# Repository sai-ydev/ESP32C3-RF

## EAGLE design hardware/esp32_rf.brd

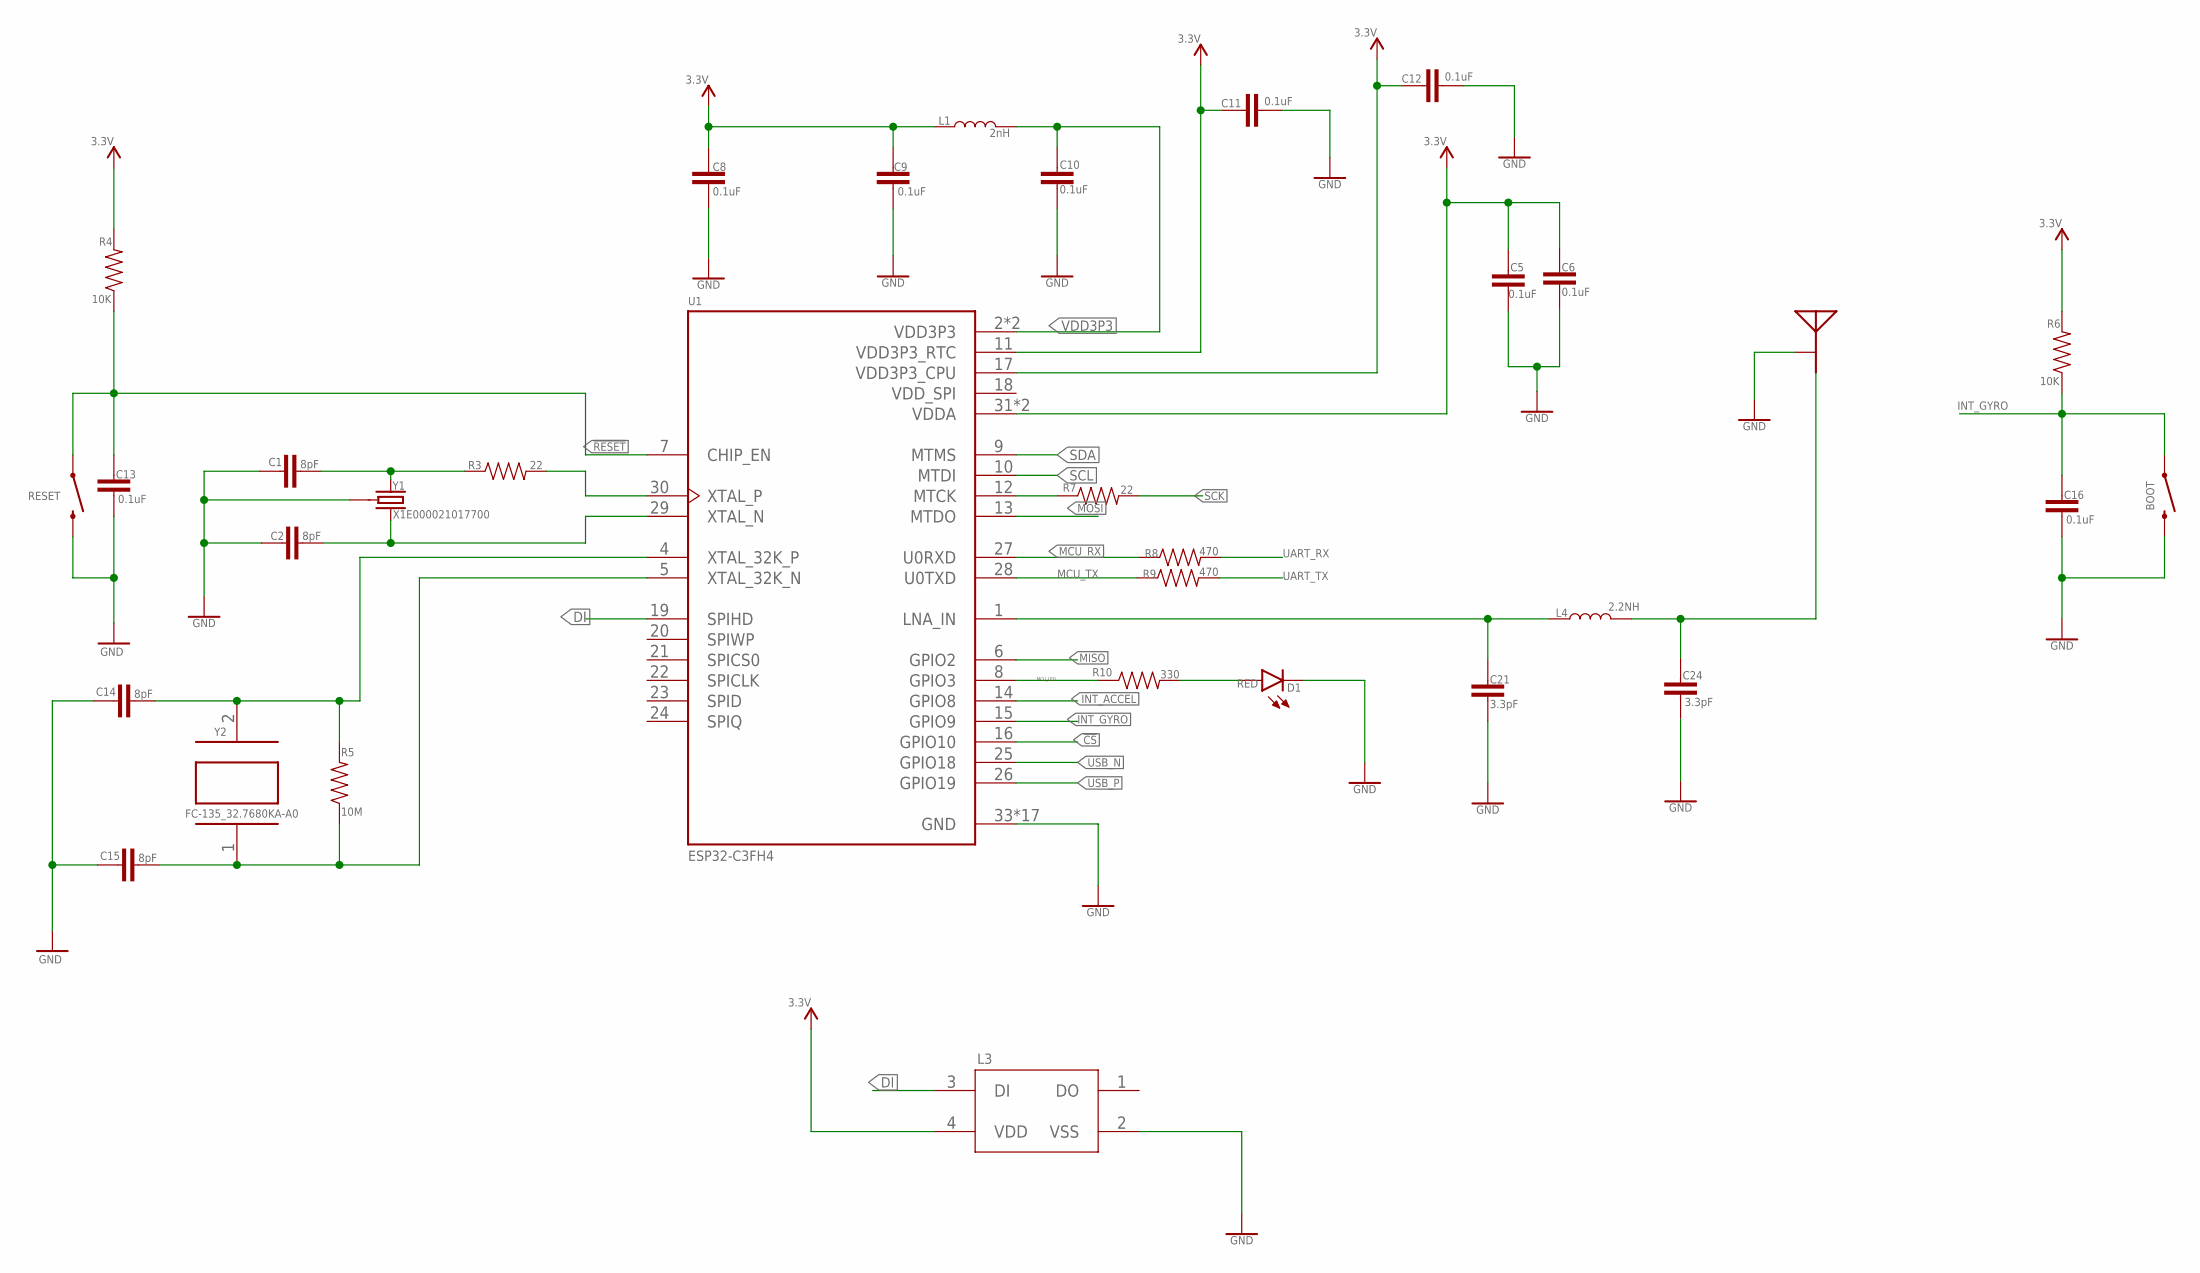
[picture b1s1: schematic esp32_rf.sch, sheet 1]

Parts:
BOOT: MOMENTARY-SWITCH-SPST-SMD-4.6X2.8MM; TACTILE_SWITCH_SMD_4.6X2.8MM
C1, C2, C14, C15: 8pF; 0402
C5, C6, C8, C9, C10, C11, C12, C13, C16: 0.1uF; 0402
C21, C24: 3.3pF; 0402
D1: RED; LED-0603
L1: 2nH; 0402
L3: WS2812B-2020
L4: 2.2NH; 0402
R3, R7: 22; 0402
R4, R6: 10K; 0402
R5: 10M; 0402
R8, R9: 470; 0402
R10: 330; 0402
RESET: MOMENTARY-SWITCH-SPST-SMD-4.6X2.8MM; TACTILE_SWITCH_SMD_4.6X2.8MM
U1: ESP32-C3FH4; QFN50P500X500X90-33N
U$1: MEANDER-ANT
Y1: X1E000021017700; CRYSTAL-SMD-3.2X2.5MM
Y2: FC-135_32.7680KA-A0; XTAL_FC-135_32.7680KA-A0

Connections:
3.3V: C5.1, C6.1, C8.1, C9.2, C11.2, C12.2, L1.1, L3.4 (VDD), R4.2, R6.2, U1.11 (VDD3P3_RTC), U1.17 (VDD3P3_CPU), U1.31 (VDDA), U1.32 (VDDA); also elsewhere on the board
!CS: U1.16 (GPIO10); also elsewhere on the board
!RESET: C13.1, R4.1, RESET.1, RESET.2 (1), U1.7 (CHIP_EN)
DI: L3.3 (DI), U1.19 (SPIHD)
GND: BOOT.3 (2), BOOT.4 (2), C1.1, C2.1, C5.2, C6.2, C8.2, C9.1, C10.1, C11.1, C12.1, C13.2, C14.1, C15.1, C16.2, C21.2, C24.2, D1.C, L3.2 (VSS), RESET.3 (2), RESET.4 (2), U1.33 (GND), U1.34 (GND), U1.35 (GND), U1.36 (GND), U1.37 (GND), U1.38 (GND), U1.39 (GND), U1.40 (GND), U1.41 (GND), U1.42 (GND), U1.43 (GND), U1.44 (GND), U1.45 (GND), U1.46 (GND), U1.47 (GND), U1.48 (GND), U1.49 (GND), U$1.GND, Y1.2 (3), Y1.4 (3); also elsewhere on the board
INT_ACCEL: U1.14 (GPIO8); also elsewhere on the board
INT_GYRO: BOOT.1, BOOT.2 (1), C16.1, R6.1, U1.15 (GPIO9); also elsewhere on the board
MCU_LED: R10.1, U1.8 (GPIO3)
MCU_RX: R8.1, U1.27 (U0RXD)
MCU_TX: R9.1, U1.28 (U0TXD)
MISO: U1.6 (GPIO2); also elsewhere on the board
MOSI: U1.13 (MTDO); also elsewhere on the board
unnamed: R3.2, U1.30 (XTAL_P)
unnamed: C1.2, R3.1, Y1.1
unnamed: C2.2, U1.29 (XTAL_N), Y1.3 (2)
unnamed: C21.1, L4.1, U1.1 (LNA_IN)
unnamed: C24.1, L4.2, U$1.FEED
unnamed: D1.A, R10.2
unnamed: C14.2, R5.2, U1.4 (XTAL_32K_P), Y2.2
unnamed: C15.2, R5.1, U1.5 (XTAL_32K_N), Y2.1
unnamed: R7.1, U1.12 (MTCK)
SCK: R7.2; also elsewhere on the board
SCL: U1.10 (MTDI); also elsewhere on the board
SDA: U1.9 (MTMS); also elsewhere on the board
UART_RX: R8.2; also elsewhere on the board
UART_TX: R9.2; also elsewhere on the board
USB_N: U1.25 (GPIO18); also elsewhere on the board
USB_P: U1.26 (GPIO19); also elsewhere on the board
VDD3P3: C10.2, L1.2, U1.2 (VDD3P3), U1.3 (VDD3P3)
VDD_SPI: U1.18 (VDD_SPI)

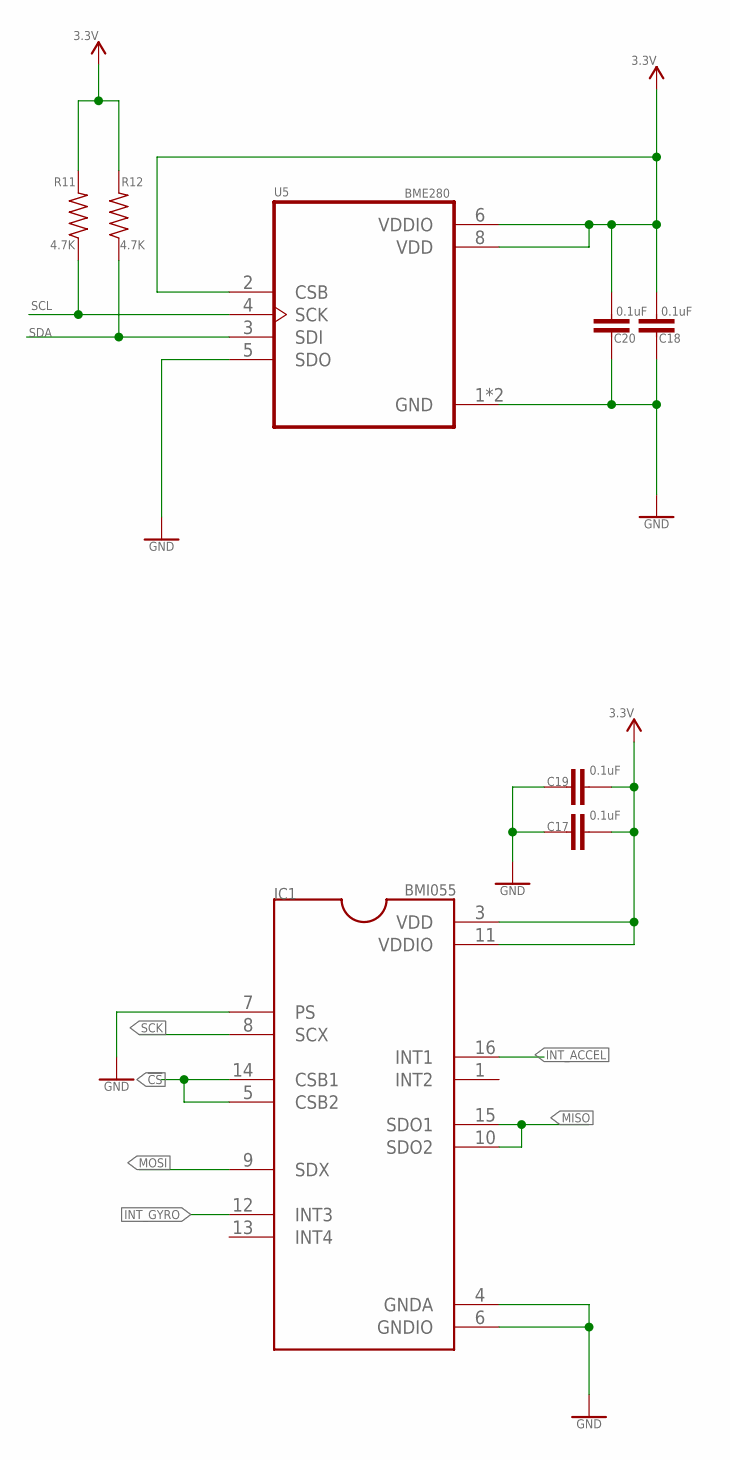
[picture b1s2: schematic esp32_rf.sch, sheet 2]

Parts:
C17, C18, C19, C20: 0.1uF; 0402
IC1: BMI055; QFN50P300X450X100-16N
R11, R12: 4.7K; 0402
U5: BME280; PSON65P250X250X100-8N

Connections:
3.3V: C17.2, C18.2, C19.2, C20.2, IC1.3 (VDD), IC1.11 (VDDIO), R11.2, R12.2, U5.2 (CSB), U5.6 (VDDIO), U5.8 (VDD); also elsewhere on the board
!CS: IC1.5 (CSB2), IC1.14 (CSB1); also elsewhere on the board
GND: C17.1, C18.1, C19.1, C20.1, IC1.4 (GNDA), IC1.6 (GNDIO), IC1.7 (PS), U5.1 (GND), U5.5 (SDO), U5.7 (GND); also elsewhere on the board
INT_ACCEL: IC1.16 (INT1); also elsewhere on the board
INT_GYRO: IC1.12 (INT3); also elsewhere on the board
MISO: IC1.10 (SDO2), IC1.15 (SDO1); also elsewhere on the board
MOSI: IC1.9 (SDX); also elsewhere on the board
SCK: IC1.8 (SCX); also elsewhere on the board
SCL: R11.1, U5.4 (SCK); also elsewhere on the board
SDA: R12.1, U5.3 (SDI); also elsewhere on the board

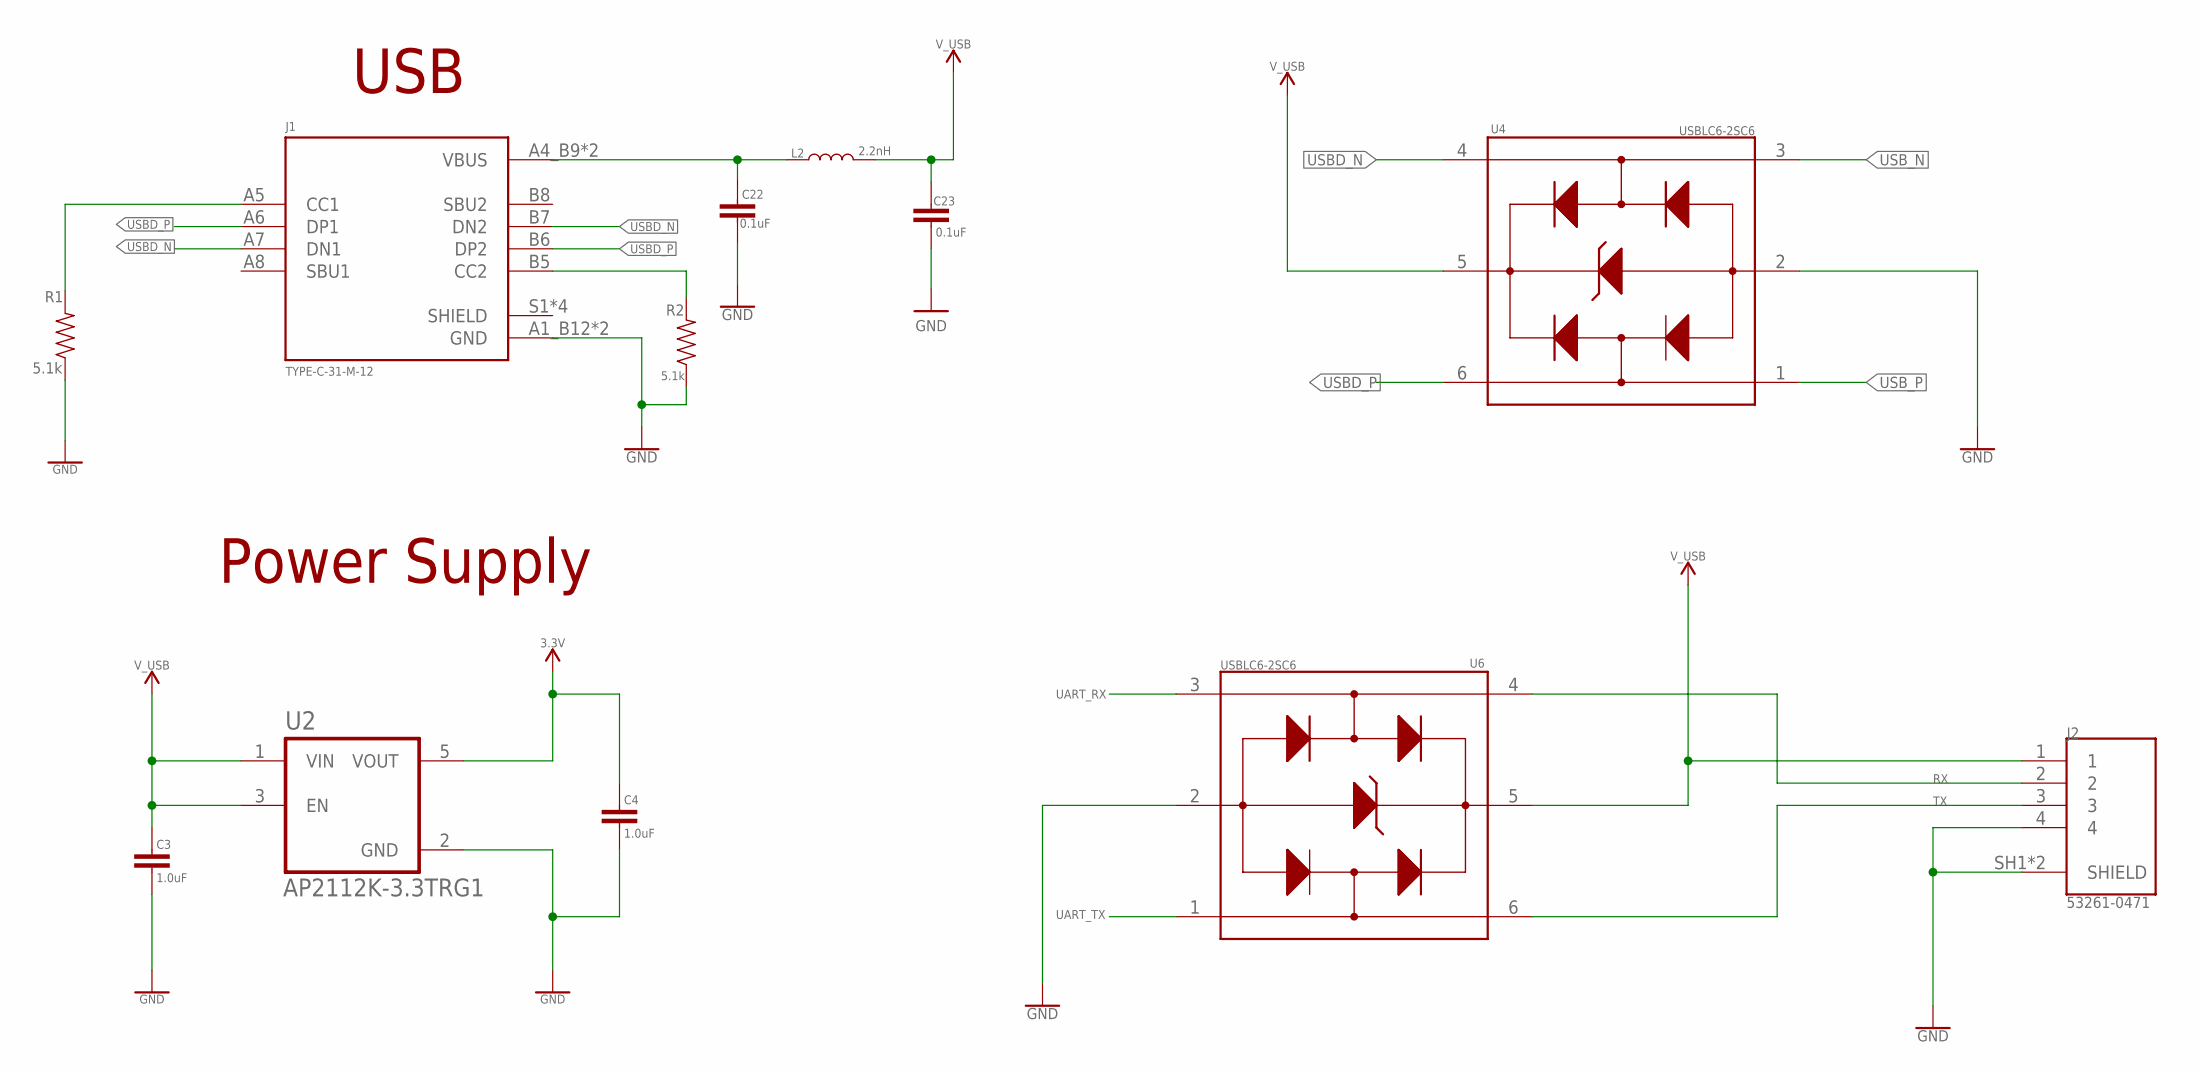
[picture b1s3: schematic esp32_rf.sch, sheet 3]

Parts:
C3, C4: 1.0uF; 0402
C22, C23: 0.1uF; 0402
J1: TYPE-C-31-M-12; HRO_TYPE-C-31-M-12
J2: 53261-0471; MOLEX_53261-0471
L2: 2.2nH; 0402
R1, R2: 5.1k; 0603
U2: AP2112K-3.3TRG1; SOT95P285X140-5N
U4, U6: USBLC6-2SC6; SOT95P280X145-6N

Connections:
3.3V: C4.1, U2.5 (VOUT); also elsewhere on the board
GND: C3.2, C4.2, C22.2, C23.2, J1.A1_B12 (GND), J1.B1_A12 (GND), J2.4, J2.SH1 (SHIELD), J2.SH2 (SHIELD), R1.1, R2.1, U2.2 (GND), U4.2 (GND), U6.2 (GND); also elsewhere on the board
unnamed: J1.A5 (CC1), R1.2
unnamed: J1.B5 (CC2), R2.2
unnamed: C22.1, J1.A4_B9 (VBUS), J1.B4_A9 (VBUS), L2.1
RX: J2.2, U6.4 (I/O2_OUT)
TX: J2.3, U6.6 (I/O1_OUT)
UART_RX: U6.3 (I/O2_IN); also elsewhere on the board
UART_TX: U6.1 (I/O1_IN); also elsewhere on the board
USBD_N: J1.A7 (DN1), J1.B7 (DN2), U4.4 (I/O2_OUT)
USBD_P: J1.A6 (DP1), J1.B6 (DP2), U4.6 (I/O1_OUT)
USB_N: U4.3 (I/O2_IN); also elsewhere on the board
USB_P: U4.1 (I/O1_IN); also elsewhere on the board
V_USB: C3.1, C23.1, J2.1, L2.2, U2.1 (VIN), U2.3 (EN), U4.5 (VBUS), U6.5 (VBUS)

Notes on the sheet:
Power Supply
USB

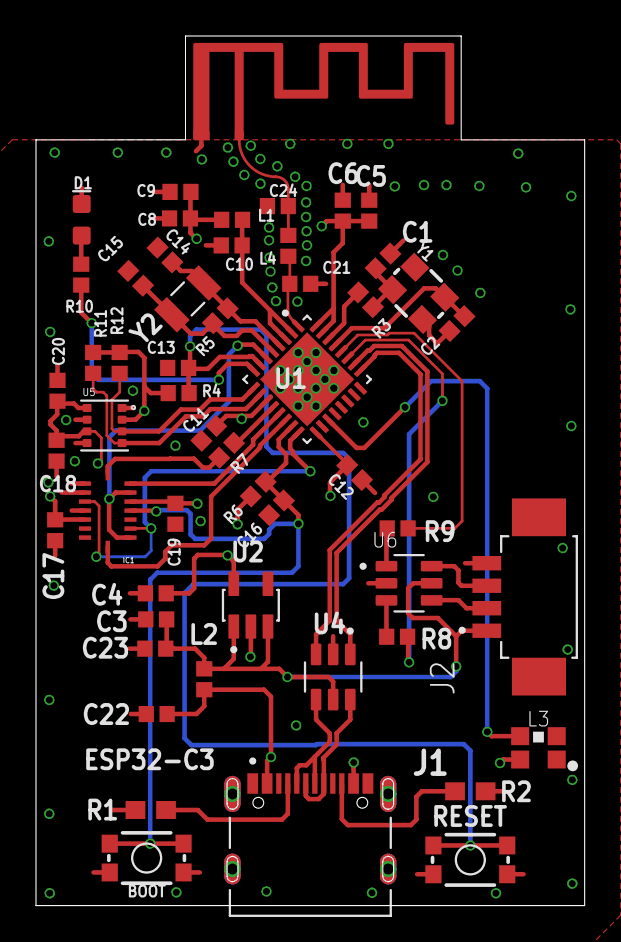
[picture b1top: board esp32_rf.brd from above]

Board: 4 copper layers, 30.5 x 48.3 mm, 53 parts (0 on the bottom side), 37 nets.

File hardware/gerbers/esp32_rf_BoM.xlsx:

Designator | Comment | Footprint | MPN
BOOT | SPST | MOMENTARY-SWITCH-SPST-SMD-4.6X2.8MM | KMR231GLFS
C1 | 8pF | 50V 8pF ±0.25pF 0402 | C0402C0G8R0C500NTB
C2 | 8pF | 50V 8pF ±0.25pF 0402 | C0402C0G8R0C500NTB
C3 | 1.0uF | 25V 1uF ±10% 0402 | 0402X105K250NT
C4 | 1.0uF | 25V 1uF ±10% 0402 | 0402X105K250NT
C5 | 0.1uF | 16V 100nF X7R ±10% 0402 | CL05B104KO5NNNC
C6 | 0.1uF | 16V 100nF X7R ±10% 0402 | CL05B104KO5NNNC
C8 | 0.1uF | 16V 100nF X7R ±10% 0402 | CL05B104KO5NNNC
C9 | 0.1uF | 16V 100nF X7R ±10% 0402 | CL05B104KO5NNNC
C10 | 0.1uF | 16V 100nF X7R ±10% 0402 | CL05B104KO5NNNC
C11 | 0.1uF | 16V 100nF X7R ±10% 0402 | CL05B104KO5NNNC
C12 | 0.1uF | 16V 100nF X7R ±10% 0402 | CL05B104KO5NNNC
C13 | 0.1uF | 16V 100nF X7R ±10% 0402 | CL05B104KO5NNNC
C14 | 8pF | 50V 8pF ±0.25pF 0402 | C0402C0G8R0C500NTB
C15 | 8pF | 50V 8pF ±0.25pF 0402 | C0402C0G8R0C500NTB
C16 | 0.1uF | 16V 100nF X7R ±10% 0402 | CL05B104KO5NNNC
C17 | 0.1uF | 16V 100nF X7R ±10% 0402 | CL05B104KO5NNNC
C18 | 0.1uF | 16V 100nF X7R ±10% 0402 | CL05B104KO5NNNC
C19 | 0.1uF | 16V 100nF X7R ±10% 0402 | CL05B104KO5NNNC
C20 | 0.1uF | 16V 100nF X7R ±10% 0402 | CL05B104KO5NNNC
C21 | 3.3pF | 16V 100nF X7R ±10% 0402 | CL05B104KO5NNNC
C22 | 0.1uF | 16V 100nF X7R ±10% 0402 | CL05B104KO5NNNC
C23 | 0.1uF | 16V 100nF X7R ±10% 0402 | CL05B104KO5NNNC
C24 | 3.3pF | 16V 100nF X7R ±10% 0402 | CL05B104KO5NNNC
D1 | RED | Red 0603 | NCD0603R1
IC1 | BMI055 | LGA-16(3x4.5) Attitude Sensor/Gyroscope | BMI055
J1 | TYPE-C-31-M-12 | 5A 1 16 Female Type-C SMD USB Connectors ROHS | TYPE-C-31-M-12
J2 | 53261-0471 | 1x4P 1 1.25mm 4 bronze SMD,P=1.25mm Wire To Board / Wire To Wire Connector | 532610471
L1 | 2nH | 2nH 0402 Inductors | BSCH001005052N0SCS
L2 | 2.2nH | 2.2nH ±0.3nH 0402 | HFM1005-2N2S
L3 | WS2812B-2020 | 12mA RGB SMD,2x2mm Light Emitting Diodes | WS2812B-2020
L4 | 2.2NH | 2.2nH ±0.3nH 0402 | HFM1005-2N2S
R1 | 5.1k | 100mW ±1% 5.1kΩ 0603 | RMC06035.1K1%N
R2 | 5.1k | 100mW ±1% 5.1kΩ 0603 | RMC06035.1K1%N
R3 | 22 | 63mW ±100ppm/℃ ±5% 22Ω 0402 | CR0402J22R0Q10Z
R4 | 10K | ±5% 10kΩ 0402 | SCR0402J0103
R5 | 10M | ±1% 10MΩ 0402 | SCR0402F10M
R6 | 10K | ±5% 10kΩ 0402 | SCR0402J0103
R7 | 22 | 63mW ±100ppm/℃ ±5% 22Ω 0402 | CR0402J22R0Q10Z
R8 | 470 | ±1% 470Ω 0402 | SCR0402F470R
R9 | 470 | ±1% 470Ω 0402 | SCR0402F470R
R10 | 330 | ±1% 330Ω 0603 | SCR0603F330R
R11 | 4.7K | ±5% 4.7kΩ 0402 | SCR0402J4K7
R12 | 4.7K | ±5% 4.7kΩ 0402 | SCR0402J4K7
RESET | SPST | MOMENTARY-SWITCH-SPST-SMD-4.6X2.8MM | KMR231GLFS
U1 | ESP32-C3FH4 | QFN-32-EP(5x5) RF Transceiver IC | ESP32-C3FH4
U2 | AP2112K-3.3TRG1 | Fixed 1 600mA 6V | AP2112K-3.3TRG1
U4 | USBLC6-2SC6 | 30kV SOT-23-6 ESD | USBLC6-2SC6
U5 | BME280 | LGA-8 Temperature and Humidity Sensor | BME280
U6 | USBLC6-2SC6 | 30kV SOT-23-6 ESD | USBLC6-2SC6
Y1 | X1E000021017700 | 40MHz SMD Crystal Resonator 9pF 40Ω ±10ppm | X1E000021017700
Y2 | FC-135_32.7680KA-A0 | 32.768kHz SMD Crystal Resonator 9pF | FC-135 32.7680KA-AC

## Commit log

2023-01-17 Updated libraries and schematic
2023-01-18 Updated schematic
2023-01-20 Design Files
2023-01-30 Design files check-in
2023-01-31 BoM files
2023-02-13 Board check-in

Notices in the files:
parts and their libraries:
SparkFun-Aesthetics: Licensing: Creative Commons ShareAlike 4.0 International - https://creativecommons.org/licenses/by-sa/4.0
